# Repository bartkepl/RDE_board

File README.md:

# RDE (Resistance DEcade)
Resistance DEcade with SCPI, UART, USB, RS485 and ETHERNET in 3U eurocard format

---
## Status : WIP

- First revision of schematic and PCB is done. 
- Creating a complementary board with a DIN 41612 connector and other interface connectors to order a complete assembly and begin work on software and interface testing.

---
## Features:
- 2 layer board
- ARM Cortex-M33 Processor in LQFP48 (STM32G431CBT6) 
- 0 - 999k&#8486; ressistor-relay matrix driven by 6x STPIC6C595
- USB 2.0
- 10/100 Ethernet (based on WIZnet W5500)
- UART
- Half-duplex RS485 
- 3U eurocard IEEE 1101.1-1998 format (160x100 mm)
----

## License and Contribution

[MIT License](/LICENSE)

Open to contributions in both software and hardware!

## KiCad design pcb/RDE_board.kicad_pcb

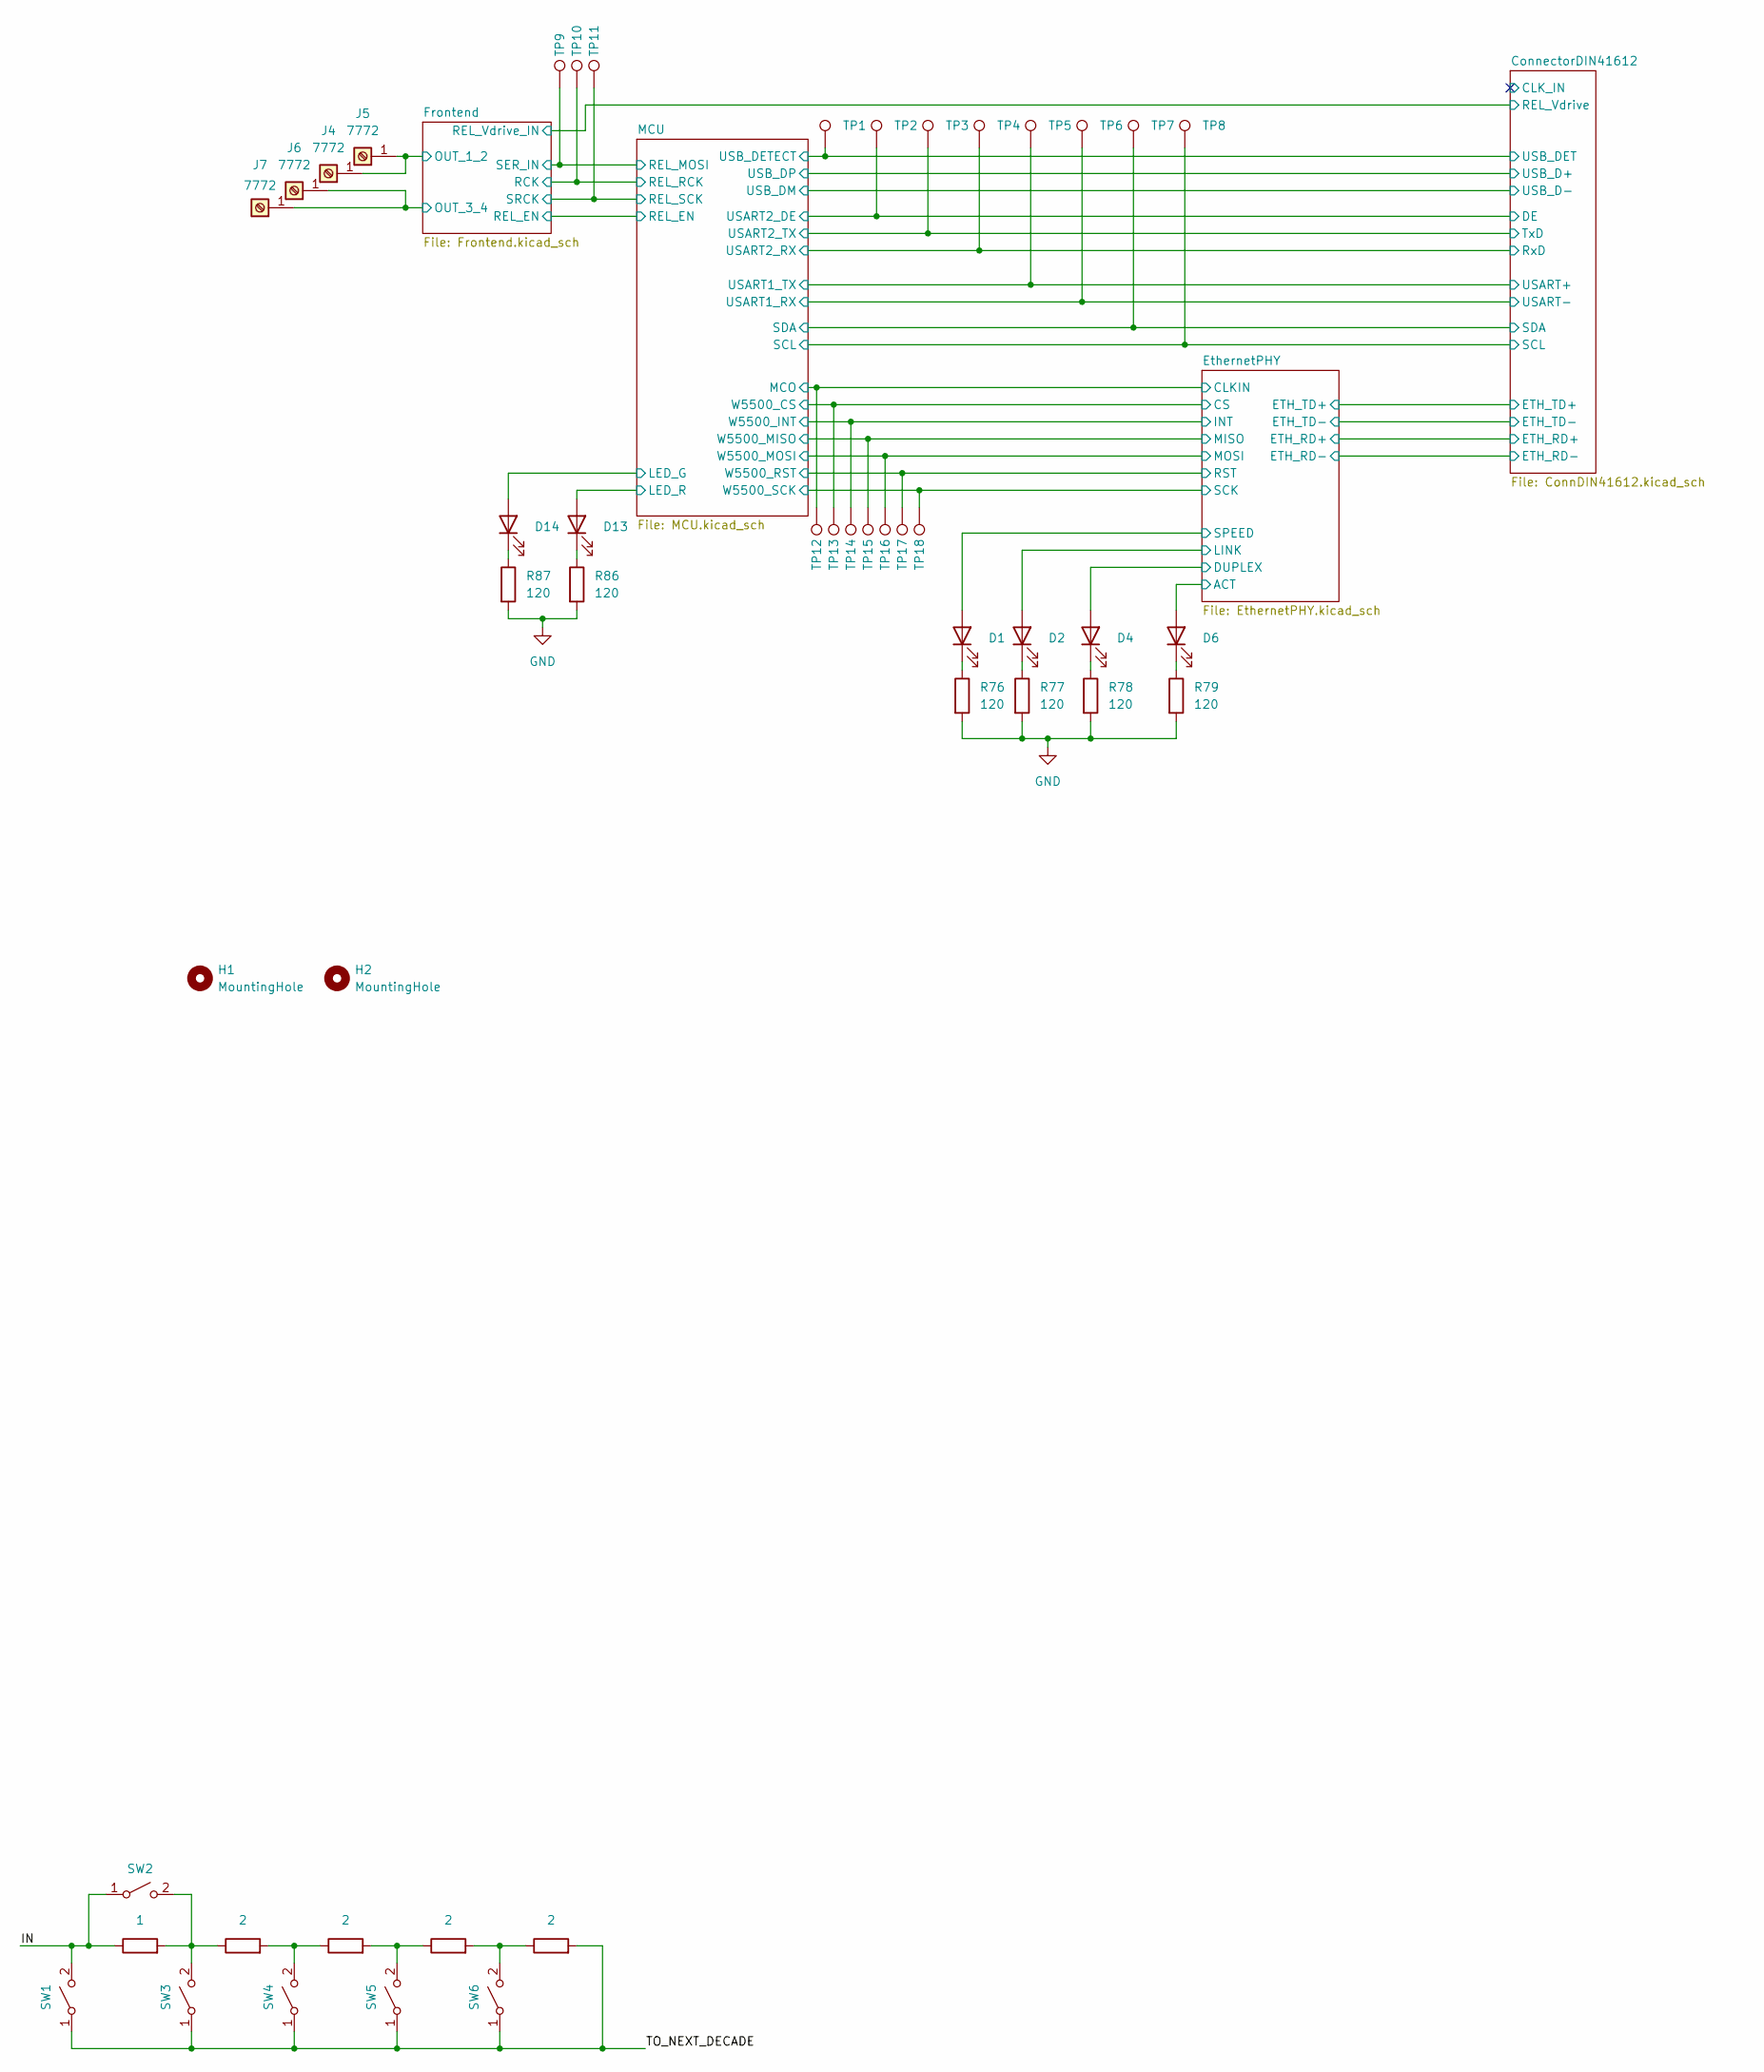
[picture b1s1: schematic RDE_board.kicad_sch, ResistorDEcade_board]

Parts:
D1, D2, D4, D6, D13, D14: LED_0603_1608Metric_Pad1.05x0.95mm_HandSolder
H1, H2: MountingHole; MountingHole_2.7mm_M2.5
J4, J5, J6, J7: 7772; Manufacturer_Part_Number 7772
R76, R77, R78, R79, R86, R87: 120; R_0603_1608Metric_Pad0.98x0.95mm_HandSolder
R92: 1; R_0603_1608Metric_Pad0.98x0.95mm_HandSolder
R93, R94, R95, R96: 2; R_0603_1608Metric_Pad0.98x0.95mm_HandSolder
SW1, SW2, SW3, SW4, SW5, SW6: SW_SPST
TP1, TP2, TP3, TP4, TP5, TP6, TP7, TP8, TP9, TP10, TP11, TP12, TP13, TP14, TP15, TP16, TP17, TP18: TestPoint; TestPoint_Pad_D1.0mm

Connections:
/ConnectorDIN41612/DE: TP2.1; also elsewhere on the board
/ConnectorDIN41612/RxD: TP4.1; also elsewhere on the board
/ConnectorDIN41612/TxD: TP3.1; also elsewhere on the board
/ConnectorDIN41612/USART+: TP5.1; also elsewhere on the board
/ConnectorDIN41612/USART-: TP6.1; also elsewhere on the board
/ConnectorDIN41612/USB_DET: TP1.1; also elsewhere on the board
/EthernetPHY/ACT: D6.2 (A); also elsewhere on the board
/EthernetPHY/CLKIN: TP12.1; also elsewhere on the board
/EthernetPHY/CS: TP13.1; also elsewhere on the board
/EthernetPHY/DUPLEX: D4.2 (A); also elsewhere on the board
/EthernetPHY/INT: TP14.1; also elsewhere on the board
/EthernetPHY/LINK: D2.2 (A); also elsewhere on the board
/EthernetPHY/MISO: TP15.1; also elsewhere on the board
/EthernetPHY/MOSI: TP16.1; also elsewhere on the board
/EthernetPHY/RST: TP17.1; also elsewhere on the board
/EthernetPHY/SCK: TP18.1; also elsewhere on the board
/EthernetPHY/SPEED: D1.2 (A); also elsewhere on the board
/Frontend/OUT_1_2: J4.1, J5.1; also elsewhere on the board
/Frontend/OUT_3_4: J6.1, J7.1; also elsewhere on the board
/Frontend/RCK: TP10.1; also elsewhere on the board
/Frontend/SER_IN: TP9.1; also elsewhere on the board
/Frontend/SRCK: TP11.1; also elsewhere on the board
/IN: R92.1, SW1.2 (B), SW2.1 (A)
/MCU/LED_G: D14.2 (A); also elsewhere on the board
/MCU/LED_R: D13.2 (A); also elsewhere on the board
/MCU/SCL: TP8.1; also elsewhere on the board
/MCU/SDA: TP7.1; also elsewhere on the board
/TO_NEXT_DECADE: R96.2, SW1.1 (A), SW3.1 (A), SW4.1 (A), SW5.1 (A), SW6.1 (A)
GND: R76.2, R77.2, R78.2, R79.2, R86.2, R87.2; also elsewhere on the board
unnamed: D1.1 (K), R76.1
unnamed: D2.1 (K), R77.1
unnamed: D4.1 (K), R78.1
unnamed: D6.1 (K), R79.1
unnamed: D13.1 (K), R86.1
unnamed: D14.1 (K), R87.1
unnamed: R92.2, R93.1, SW2.2 (B), SW3.2 (B)
unnamed: R93.2, R94.1, SW4.2 (B)
unnamed: R94.2, R95.1, SW5.2 (B)
unnamed: R95.2, R96.1, SW6.2 (B)

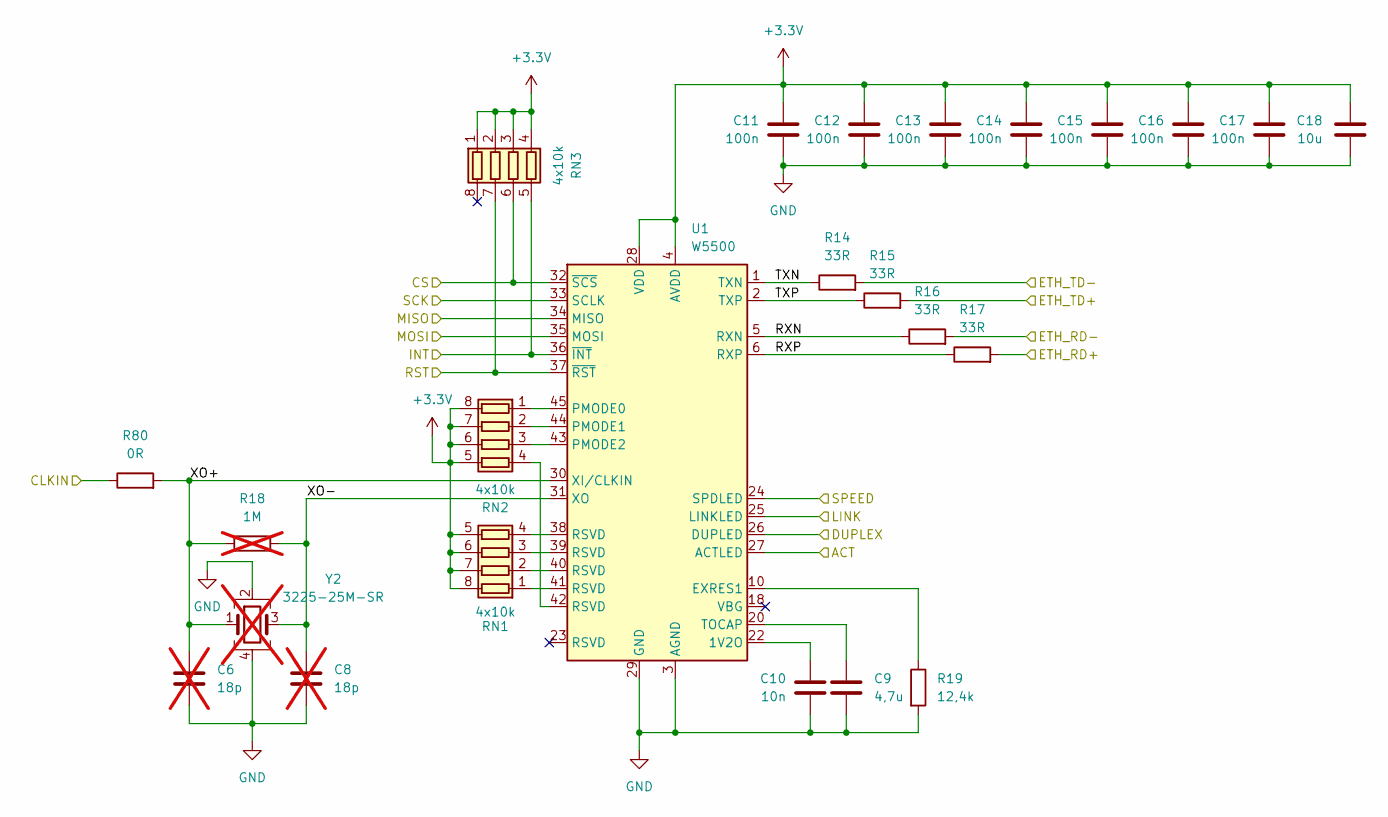
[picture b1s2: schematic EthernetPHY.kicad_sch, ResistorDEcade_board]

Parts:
C6, C8: 18p; C_0402_1005Metric_Pad0.74x0.62mm_HandSolder; not fitted
C9: 4,7u; C_0603_1608Metric_Pad1.08x0.95mm_HandSolder
C10: 10n; C_0603_1608Metric_Pad1.08x0.95mm_HandSolder
C11, C12, C13, C14, C15, C16, C17: 100n; C_0603_1608Metric_Pad1.08x0.95mm_HandSolder
C18: 10u; C_1206_3216Metric_Pad1.33x1.80mm_HandSolder
R14, R15, R16, R17: 33R; R_0603_1608Metric_Pad0.98x0.95mm_HandSolder
R18: 1M; R_0402_1005Metric_Pad0.72x0.64mm_HandSolder; not fitted
R19: 12,4k; R_0603_1608Metric_Pad0.98x0.95mm_HandSolder
R80: 0R; R_0402_1005Metric_Pad0.72x0.64mm_HandSolder
RN1, RN2, RN3: 4x10k; R_Array_Convex_4x0603
U1: W5500; LQFP-48_7x7mm_P0.5mm
Y2: 3225-25M-SR; Crystal_SMD_3225-4Pin_3.2x2.5mm; not fitted

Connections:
+3.3V: C11.2, C12.2, C13.2, C14.2, C15.2, C16.2, C17.2, C18.1, RN1.5 (R4.2), RN1.6 (R3.2), RN1.7 (R2.2), RN1.8 (R1.2), RN2.5 (R4.2), RN2.6 (R3.2), RN2.7 (R2.2), RN2.8 (R1.2), RN3.1 (R1.1), RN3.2 (R2.1), RN3.3 (R3.1), RN3.4 (R4.1), U1.4 (AVDD), U1.8 (AVDD), U1.11 (AVDD), U1.15 (AVDD), U1.17 (AVDD), U1.21 (AVDD), U1.28 (VDD); also elsewhere on the board
/ConnectorDIN41612/ETH_RD+: R17.2; also elsewhere on the board
/ConnectorDIN41612/ETH_RD-: R16.2; also elsewhere on the board
/ConnectorDIN41612/ETH_TD+: R15.2; also elsewhere on the board
/ConnectorDIN41612/ETH_TD-: R14.2; also elsewhere on the board
/EthernetPHY/ACT: U1.27 (ACTLED); also elsewhere on the board
/EthernetPHY/CLKIN: R80.1; also elsewhere on the board
/EthernetPHY/CS: RN3.6 (R3.2), U1.32 (~SCS); also elsewhere on the board
/EthernetPHY/DUPLEX: U1.26 (DUPLED); also elsewhere on the board
/EthernetPHY/INT: RN3.5 (R4.2), U1.36 (~INT); also elsewhere on the board
/EthernetPHY/LINK: U1.25 (LINKLED); also elsewhere on the board
/EthernetPHY/MISO: U1.34 (MISO); also elsewhere on the board
/EthernetPHY/MOSI: U1.35 (MOSI); also elsewhere on the board
/EthernetPHY/RST: RN3.7 (R2.2), U1.37 (~RST); also elsewhere on the board
/EthernetPHY/RXN: R16.1, U1.5 (RXN)
/EthernetPHY/RXP: R17.1, U1.6 (RXP)
/EthernetPHY/SCK: U1.33 (SCLK); also elsewhere on the board
/EthernetPHY/SPEED: U1.24 (SPDLED); also elsewhere on the board
/EthernetPHY/TXN: R14.1, U1.1 (TXN)
/EthernetPHY/TXP: R15.1, U1.2 (TXP)
/EthernetPHY/XO+: C6.1, R18.1, R80.2, U1.30 (XI/CLKIN), Y2.1
/EthernetPHY/XO-: C8.1, R18.2, U1.31 (XO), Y2.3
GND: C6.2, C8.2, C9.2, C10.1, C11.1, C12.1, C13.1, C14.1, C15.1, C16.1, C17.1, C18.2, R19.2, U1.3 (AGND), U1.9 (AGND), U1.14 (AGND), U1.16 (AGND), U1.19 (AGND), U1.29 (GND), U1.48 (AGND), Y2.2, Y2.4; also elsewhere on the board
unnamed: RN1.1 (R1.1), U1.41 (RSVD)
unnamed: RN1.2 (R2.1), U1.40 (RSVD)
unnamed: RN1.3 (R3.1), U1.39 (RSVD)
unnamed: RN1.4 (R4.1), U1.38 (RSVD)
unnamed: RN2.1 (R1.1), U1.45 (PMODE0)
unnamed: RN2.2 (R2.1), U1.44 (PMODE1)
unnamed: RN2.3 (R3.1), U1.43 (PMODE2)
unnamed: RN2.4 (R4.1), U1.42 (RSVD)
unnamed: C10.2, U1.22 (1V2O)
unnamed: R19.1, U1.10 (EXRES1)
unnamed: C9.1, U1.20 (TOCAP)

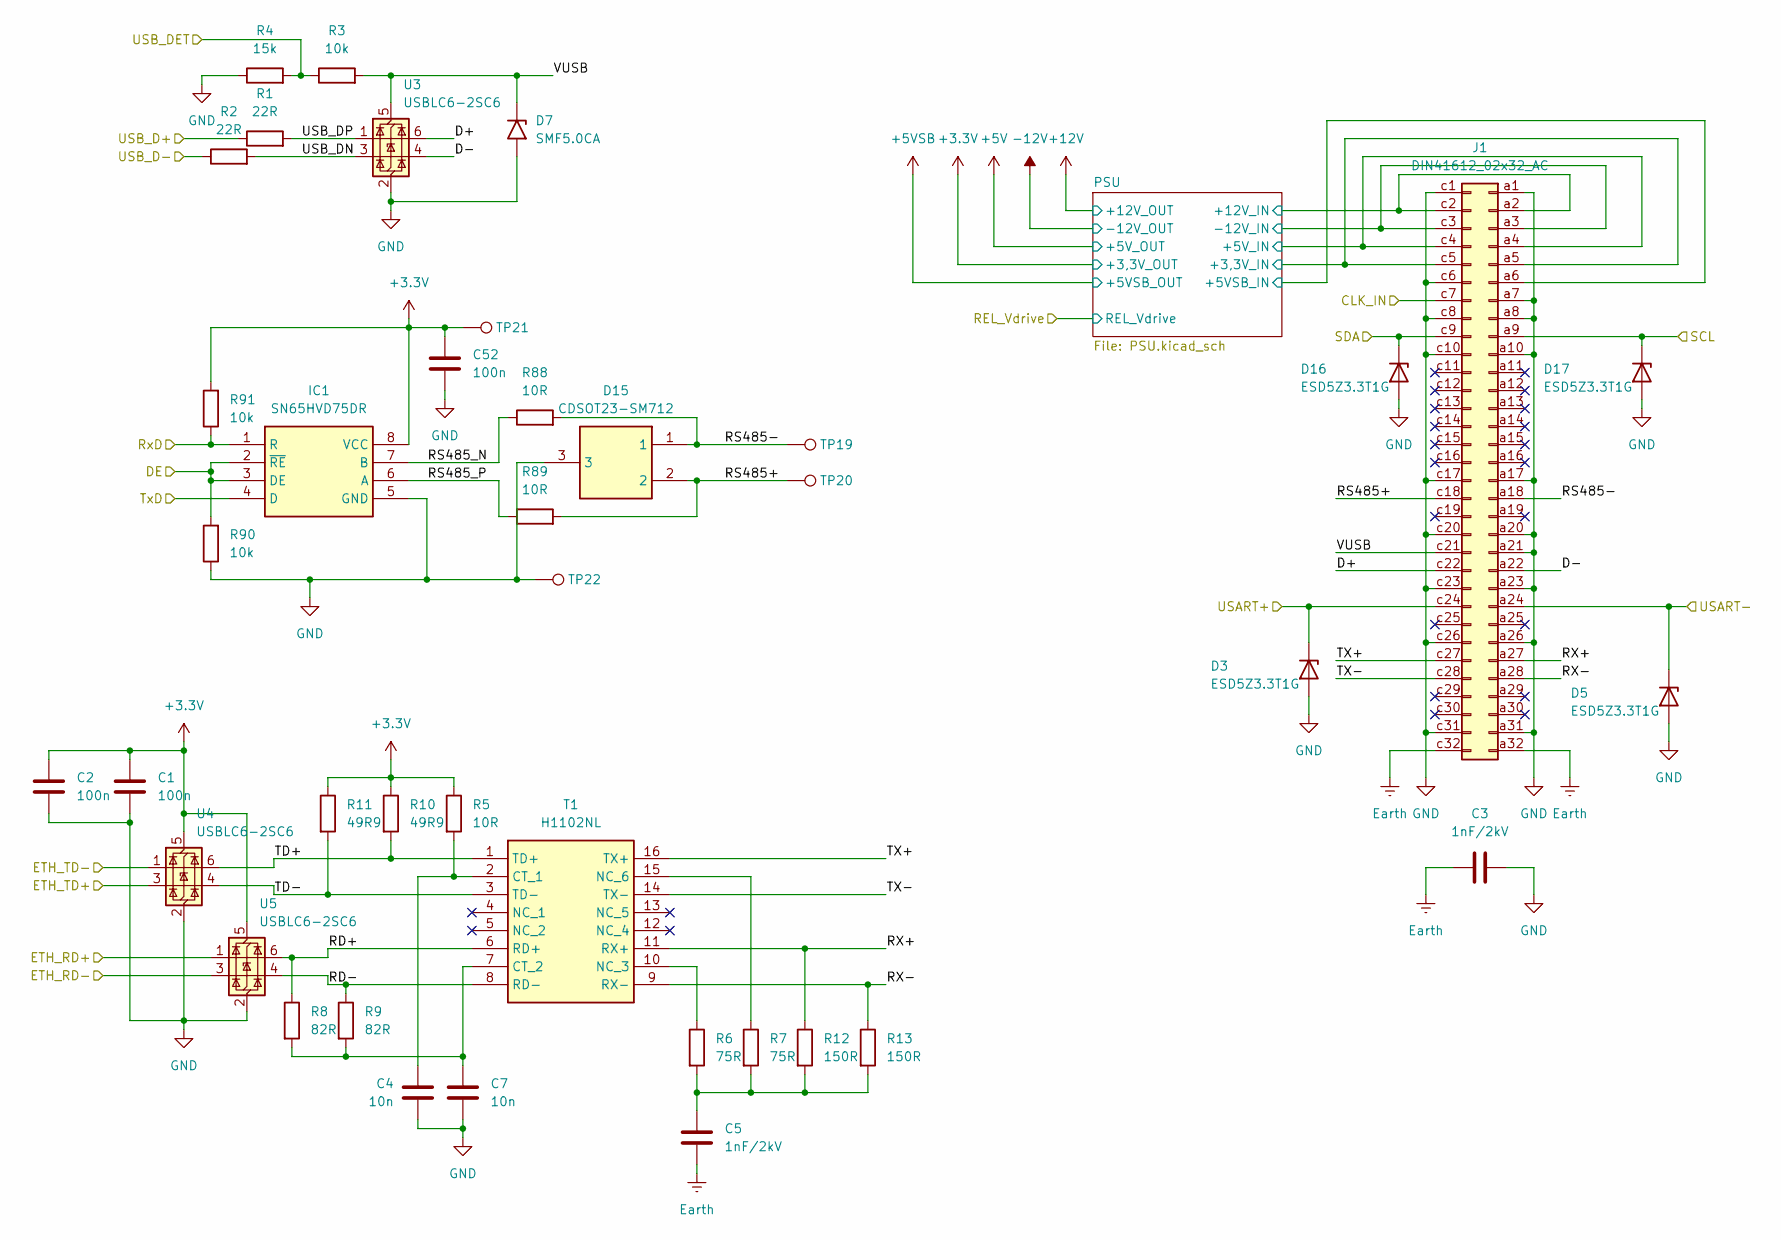
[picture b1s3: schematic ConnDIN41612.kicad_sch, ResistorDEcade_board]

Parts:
C1, C2, C52: 100n; C_0603_1608Metric_Pad1.08x0.95mm_HandSolder
C3, C5: 1nF/2kV; C_1206_3216Metric_Pad1.33x1.80mm_HandSolder
C4, C7: 10n; C_0603_1608Metric_Pad1.08x0.95mm_HandSolder
D3, D5, D16, D17: ESD5Z3.3T1G; D_SOD-523
D7: SMF5.0CA; D_SMF
D15: CDSOT23-SM712; SOT95P230X117-3N; Manufacturer_Part_Number CDSOT23-SM712
IC1: SN65HVD75DR; SOIC127P600X175-8N; Manufacturer_Part_Number SN65HVD75DR
J1: DIN41612_02x32_AC; DIN41612_C_2x32_Male_Horizontal_THT
R1, R2: 22R; R_0402_1005Metric_Pad0.72x0.64mm_HandSolder
R3, R90, R91: 10k; R_0603_1608Metric_Pad0.98x0.95mm_HandSolder
R4: 15k; R_0603_1608Metric_Pad0.98x0.95mm_HandSolder
R5, R88, R89: 10R; R_0603_1608Metric_Pad0.98x0.95mm_HandSolder
R6, R7: 75R; R_0603_1608Metric_Pad0.98x0.95mm_HandSolder
R8, R9: 82R; R_0603_1608Metric_Pad0.98x0.95mm_HandSolder
R10, R11: 49R9; R_0603_1608Metric_Pad0.98x0.95mm_HandSolder
R12, R13: 150R; R_0603_1608Metric_Pad0.98x0.95mm_HandSolder
T1: H1102NL; SOIC127P940X597-16N; Manufacturer_Part_Number H1102NL
TP19, TP20, TP21, TP22: TestPoint; TestPoint_Pad_D1.0mm
U3, U4, U5: USBLC6-2SC6; SOT-23-6_Handsoldering

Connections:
+3.3V: C1.1, C2.1, C52.1, IC1.8 (VCC), R5.1, R10.1, R11.1, R91.2, TP21.1, U4.5 (VBUS), U5.5 (VBUS); also elsewhere on the board
/ConnectorDIN41612/CLK_IN: J1.c7
/ConnectorDIN41612/D+: J1.c22, U3.6 (I/O1)
/ConnectorDIN41612/D-: J1.a22, U3.4 (I/O2)
/ConnectorDIN41612/DE: IC1.2 (~RE), IC1.3 (DE), R90.2; also elsewhere on the board
/ConnectorDIN41612/ETH_RD+: U5.1 (I/O1); also elsewhere on the board
/ConnectorDIN41612/ETH_RD-: U5.3 (I/O2); also elsewhere on the board
/ConnectorDIN41612/ETH_TD+: U4.3 (I/O2); also elsewhere on the board
/ConnectorDIN41612/ETH_TD-: U4.1 (I/O1); also elsewhere on the board
/ConnectorDIN41612/PSU/+3,3V_IN: J1.a5, J1.c5; also elsewhere on the board
/ConnectorDIN41612/PSU/+5VSB_IN: J1.a6
/ConnectorDIN41612/PSU/+5V_IN: J1.a4, J1.c4; also elsewhere on the board
/ConnectorDIN41612/PSU/+12V_IN: J1.a2, J1.c2
/ConnectorDIN41612/PSU/-12V_IN: J1.a3, J1.c3
/ConnectorDIN41612/RD+: R8.1, T1.6 (RD+), U5.6 (I/O1)
/ConnectorDIN41612/RD-: R9.1, T1.8 (RD-), U5.4 (I/O2)
/ConnectorDIN41612/RS485+: D15.2, J1.c18, R89.2, TP20.1
/ConnectorDIN41612/RS485-: D15.1, J1.a18, R88.2, TP19.1
/ConnectorDIN41612/RS485_N: IC1.7 (B), R88.1
/ConnectorDIN41612/RS485_P: IC1.6 (A), R89.1
/ConnectorDIN41612/RX+: J1.a27, R12.1, T1.11 (RX+)
/ConnectorDIN41612/RX-: J1.a28, R13.1, T1.9 (RX-)
/ConnectorDIN41612/RxD: IC1.1 (R), R91.1; also elsewhere on the board
/ConnectorDIN41612/TD+: R10.2, T1.1 (TD+), U4.6 (I/O1)
/ConnectorDIN41612/TD-: R11.2, T1.3 (TD-), U4.4 (I/O2)
/ConnectorDIN41612/TX+: J1.c27, T1.16 (TX+)
/ConnectorDIN41612/TX-: J1.c28, T1.14 (TX-)
/ConnectorDIN41612/TxD: IC1.4 (D); also elsewhere on the board
/ConnectorDIN41612/USART+: D3.1 (K), J1.c24; also elsewhere on the board
/ConnectorDIN41612/USART-: D5.1 (K), J1.a24; also elsewhere on the board
/ConnectorDIN41612/USB_D+: R1.1; also elsewhere on the board
/ConnectorDIN41612/USB_D-: R2.1; also elsewhere on the board
/ConnectorDIN41612/USB_DET: R3.1, R4.2; also elsewhere on the board
/ConnectorDIN41612/USB_DN: R2.2, U3.3 (I/O2)
/ConnectorDIN41612/USB_DP: R1.2, U3.1 (I/O1)
/ConnectorDIN41612/VUSB: D7.1 (A1), J1.c21, R3.2, U3.5 (VBUS)
/MCU/SCL: D17.1 (K), J1.a9; also elsewhere on the board
/MCU/SDA: D16.1 (K), J1.c9; also elsewhere on the board
Earth: C3.1, C5.2, J1.a32, J1.c32
GND: C1.2, C2.2, C3.2, C4.1, C7.2, C52.2, D3.2 (A), D5.2 (A), D7.2 (A2), D15.3, D16.2 (A), D17.2 (A), IC1.5 (GND), J1.a1, J1.a7, J1.a8, J1.a10, J1.a17, J1.a20, J1.a21, J1.a23, J1.a26, J1.a31, J1.c1, J1.c6, J1.c8, J1.c10, J1.c17, J1.c20, J1.c23, J1.c26, J1.c31, R4.1, R90.1, TP22.1, U3.2 (GND), U4.2 (GND), U5.2 (GND); also elsewhere on the board
unnamed: C5.1, R6.2, R7.2, R12.2, R13.2
unnamed: C4.2, R5.2, T1.2 (CT_1)
unnamed: C7.1, R8.2, R9.2, T1.7 (CT_2)
unnamed: R6.1, T1.10 (NC_3)
unnamed: R7.1, T1.15 (NC_6)

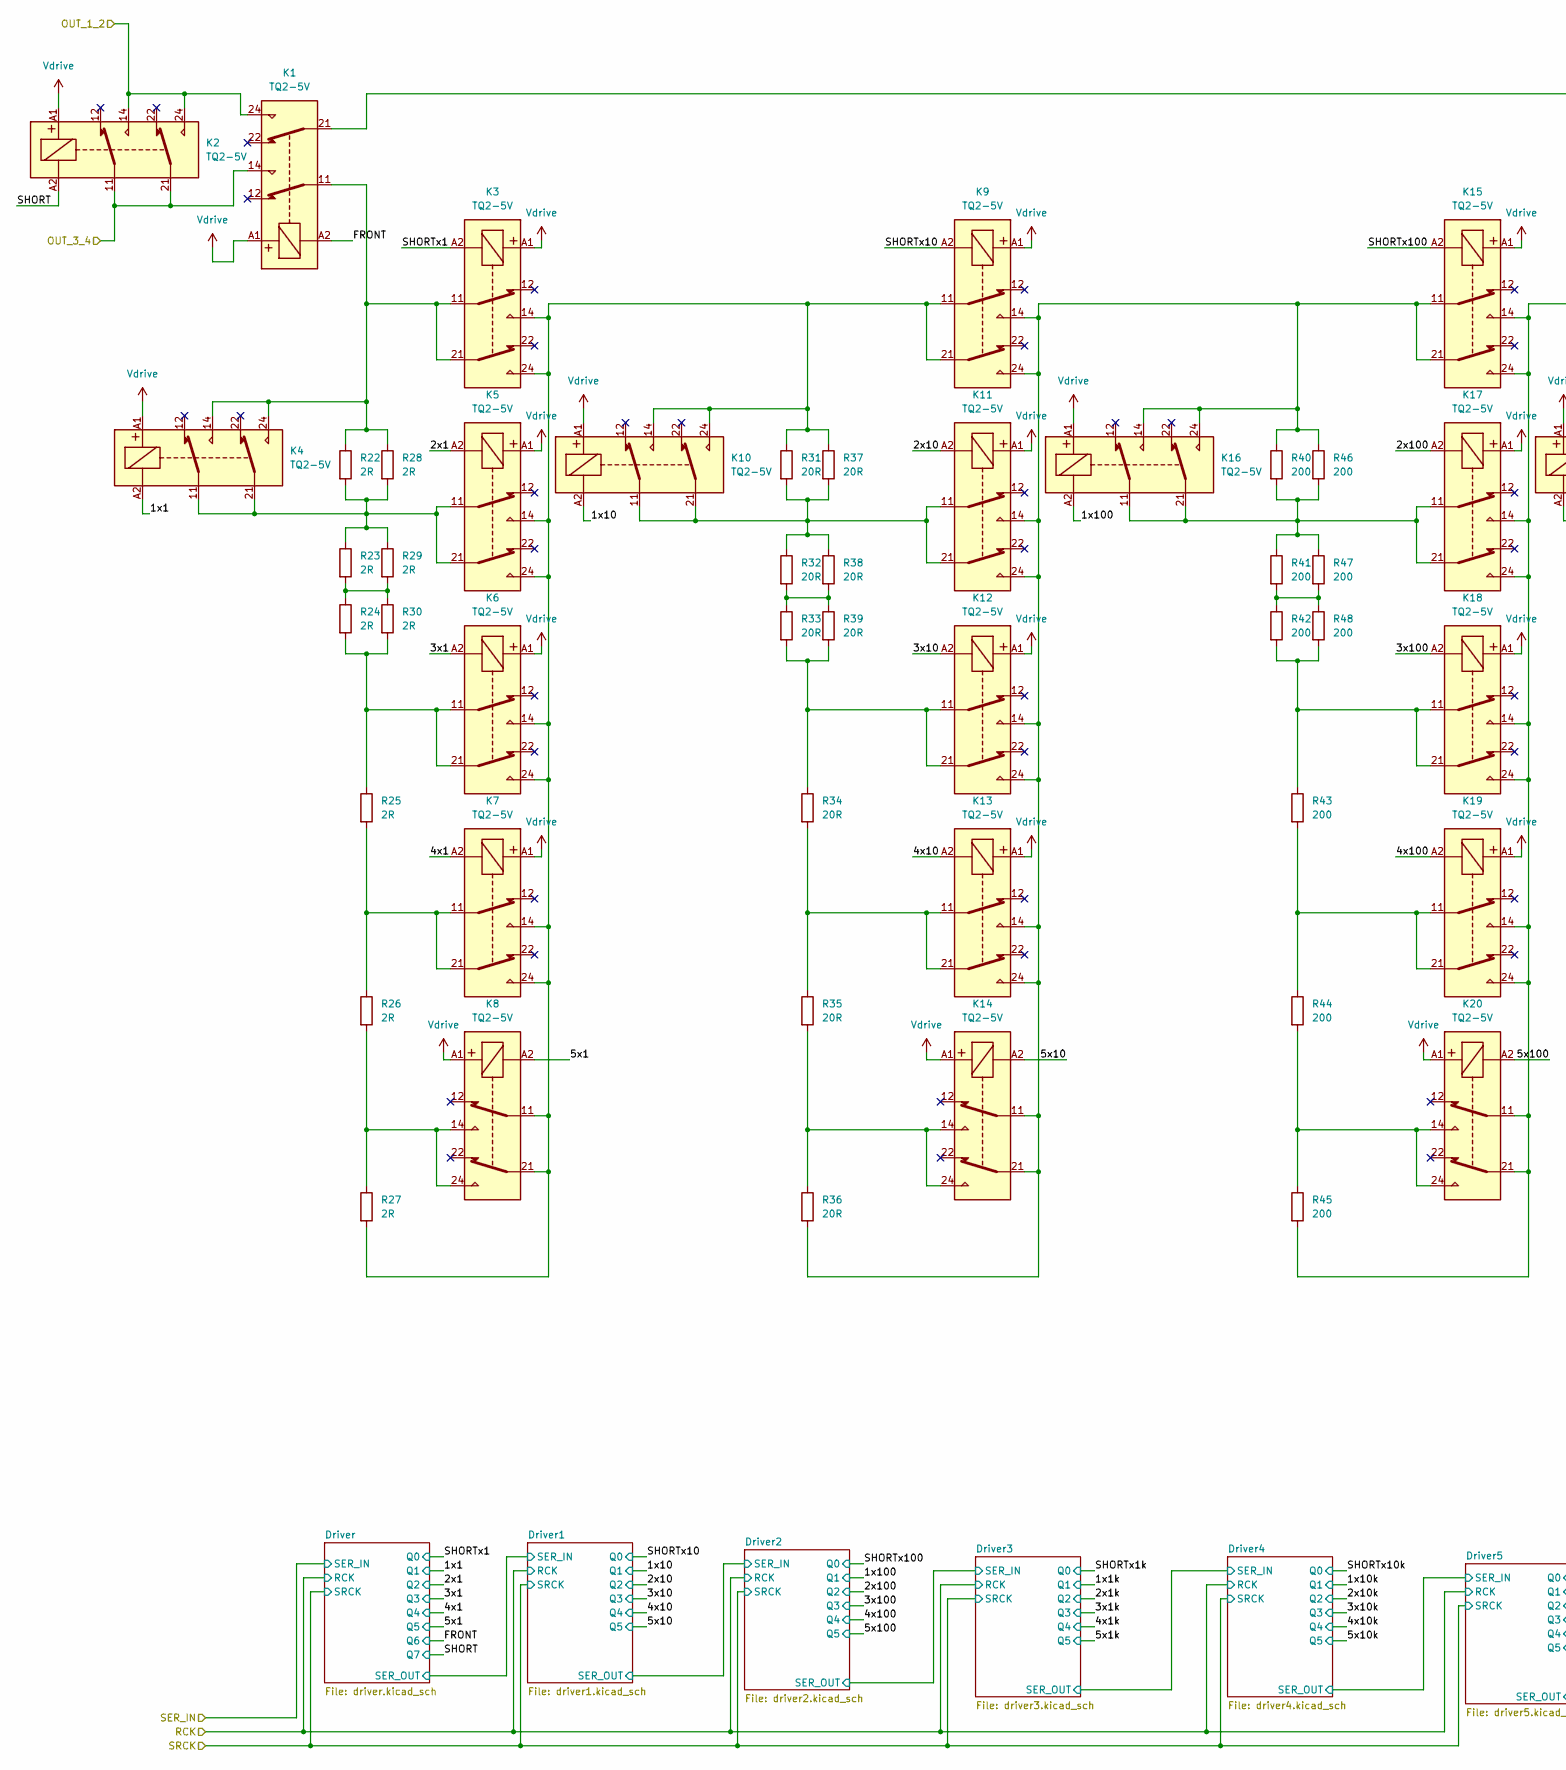
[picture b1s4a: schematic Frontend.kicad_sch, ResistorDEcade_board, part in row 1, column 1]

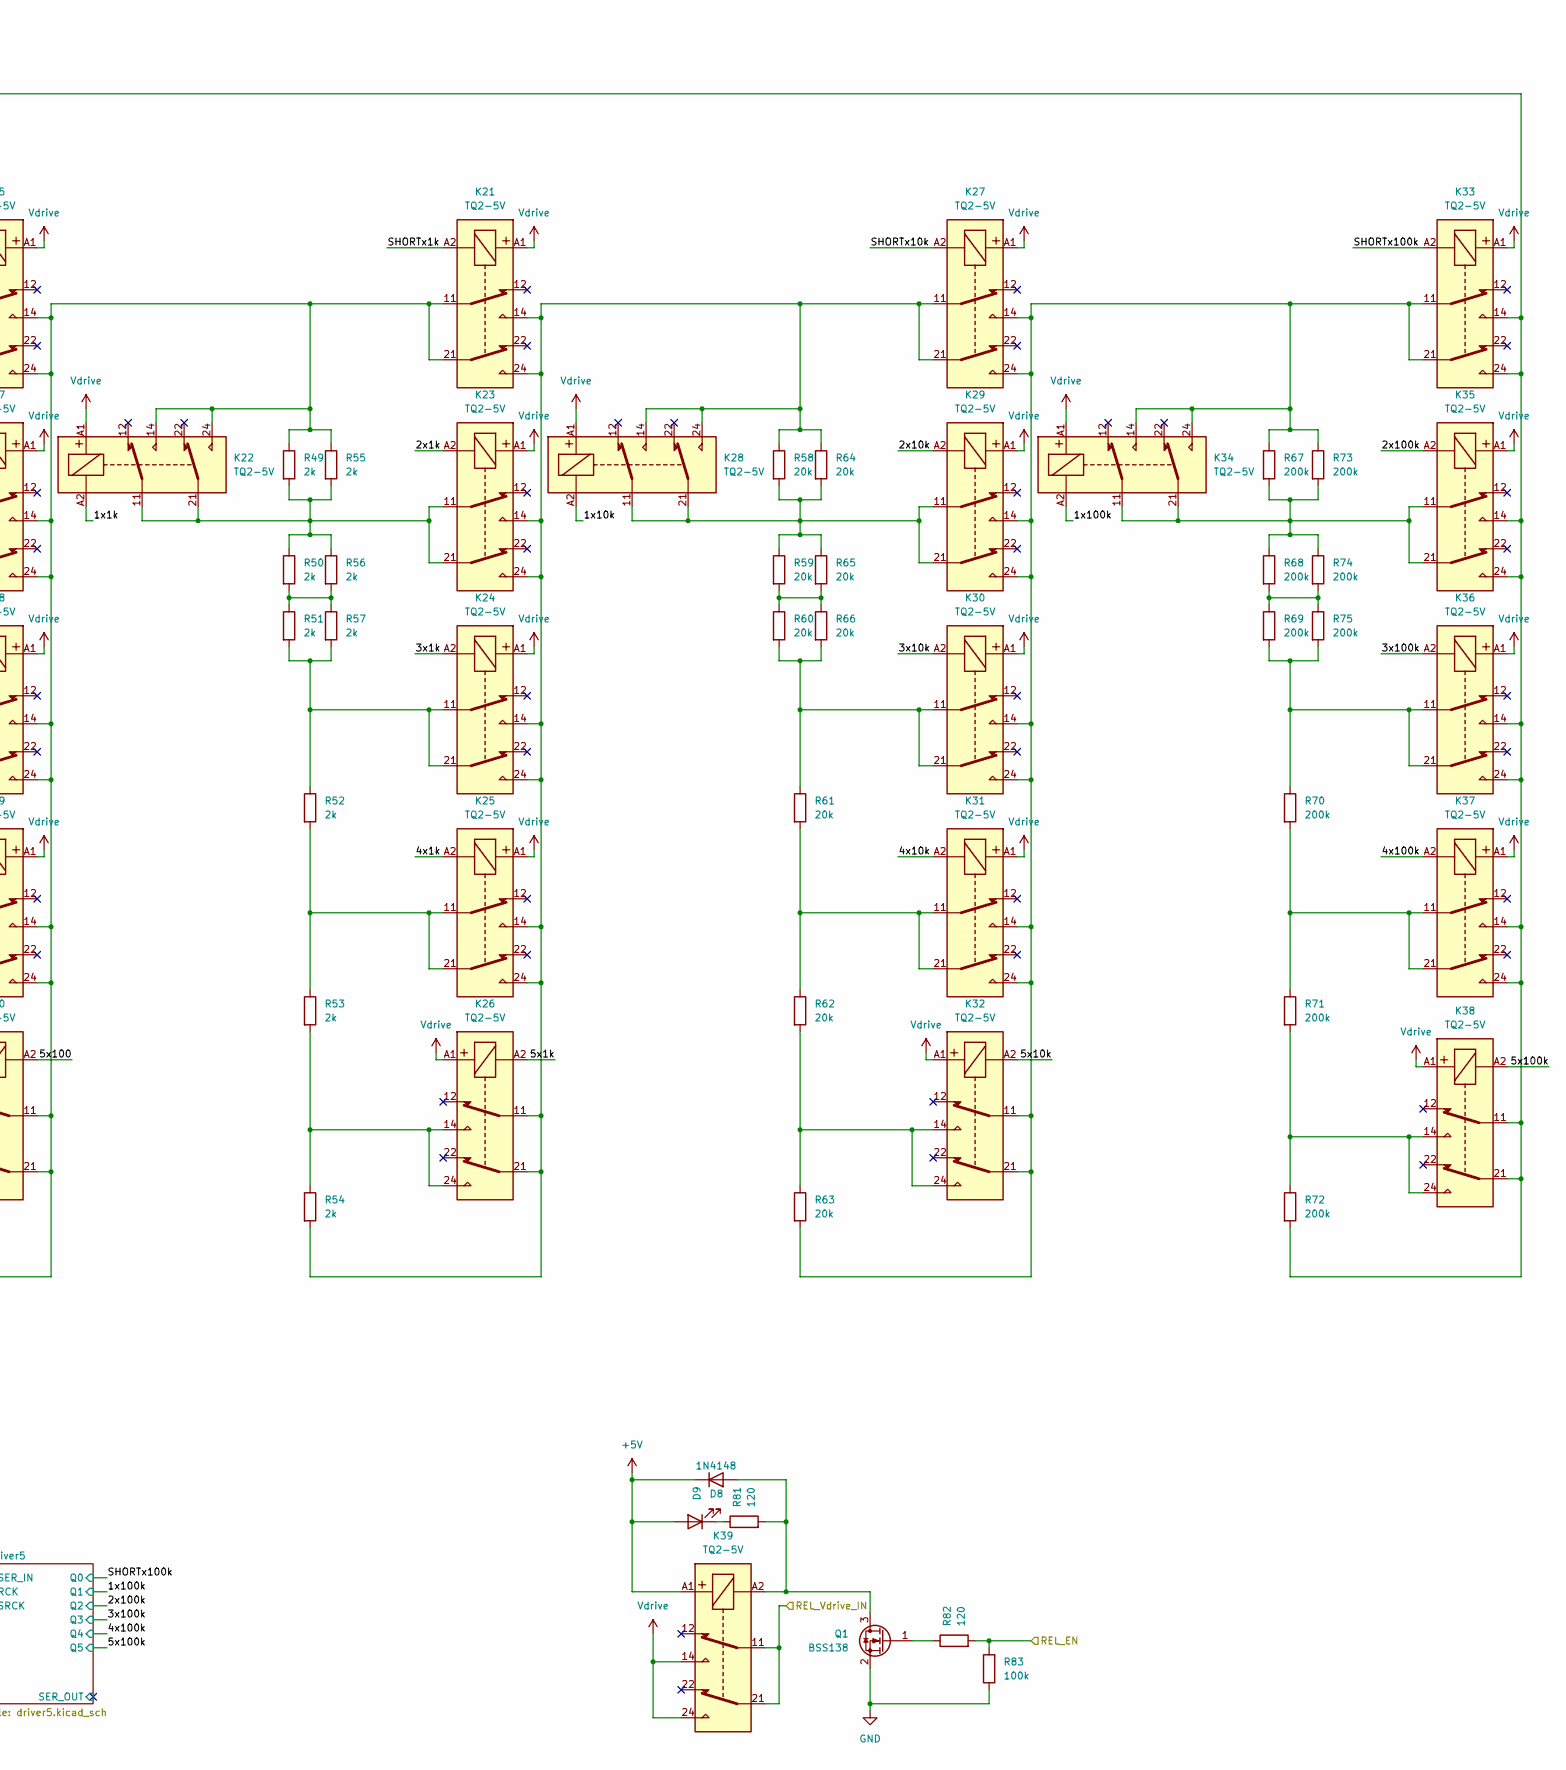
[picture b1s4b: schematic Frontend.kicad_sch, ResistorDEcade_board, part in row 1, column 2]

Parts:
D8: 1N4148; D_MiniMELF
D9: LED_0603_1608Metric_Pad1.05x0.95mm_HandSolder
K1, K2, K3, K4, K5, K6, K7, K8, K9, K10, K11, K12, K13, K14, K15, K16, K17, K18, K19, K20, K21, K22, K23, K24, K25, K26, K27, K28, K29, K30, K31, K32, K33, K34, K35, K36, K37, K38, K39: TQ2-5V; TX2L25V; Manufacturer_Part_Number TQ2-5V
Q1: BSS138; SOT-23
R22, R23, R24, R25, R26, R27, R28, R29, R30: 2R; R_0603_1608Metric_Pad0.98x0.95mm_HandSolder
R31, R32, R33, R34, R35, R36, R37, R38, R39: 20R; R_0603_1608Metric_Pad0.98x0.95mm_HandSolder
R40, R41, R42, R43, R44, R45, R46, R47, R48: 200; R_0603_1608Metric_Pad0.98x0.95mm_HandSolder
R49, R50, R51, R52, R53, R54, R55, R56, R57: 2k; R_0603_1608Metric_Pad0.98x0.95mm_HandSolder
R58, R59, R60, R61, R62, R63, R64, R65, R66: 20k; R_0603_1608Metric_Pad0.98x0.95mm_HandSolder
R67, R68, R69, R70, R71, R72, R73, R74, R75: 200k; R_0603_1608Metric_Pad0.98x0.95mm_HandSolder
R81, R82: 120; R_0603_1608Metric_Pad0.98x0.95mm_HandSolder
R83: 100k; R_0603_1608Metric_Pad0.98x0.95mm_HandSolder

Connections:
+5V: D8.1 (K), D9.2 (A), K39.A1; also elsewhere on the board
/ConnectorDIN41612/REL_Vdrive: K39.11, K39.21; also elsewhere on the board
/Frontend/1x1: K4.A2; also elsewhere on the board
/Frontend/1x1k: K22.A2; also elsewhere on the board
/Frontend/1x10: K10.A2; also elsewhere on the board
/Frontend/1x10k: K28.A2; also elsewhere on the board
/Frontend/1x100: K16.A2; also elsewhere on the board
/Frontend/1x100k: K34.A2; also elsewhere on the board
/Frontend/2x1: K5.A2; also elsewhere on the board
/Frontend/2x1k: K23.A2; also elsewhere on the board
/Frontend/2x10: K11.A2; also elsewhere on the board
/Frontend/2x10k: K29.A2; also elsewhere on the board
/Frontend/2x100: K17.A2; also elsewhere on the board
/Frontend/2x100k: K35.A2; also elsewhere on the board
/Frontend/3x1: K6.A2; also elsewhere on the board
/Frontend/3x1k: K24.A2; also elsewhere on the board
/Frontend/3x10: K12.A2; also elsewhere on the board
/Frontend/3x10k: K30.A2; also elsewhere on the board
/Frontend/3x100: K18.A2; also elsewhere on the board
/Frontend/3x100k: K36.A2; also elsewhere on the board
/Frontend/4x1: K7.A2; also elsewhere on the board
/Frontend/4x1k: K25.A2; also elsewhere on the board
/Frontend/4x10: K13.A2; also elsewhere on the board
/Frontend/4x10k: K31.A2; also elsewhere on the board
/Frontend/4x100: K19.A2; also elsewhere on the board
/Frontend/4x100k: K37.A2; also elsewhere on the board
/Frontend/5x1: K8.A2; also elsewhere on the board
/Frontend/5x1k: K26.A2; also elsewhere on the board
/Frontend/5x10: K14.A2; also elsewhere on the board
/Frontend/5x10k: K32.A2; also elsewhere on the board
/Frontend/5x100: K20.A2; also elsewhere on the board
/Frontend/5x100k: K38.A2; also elsewhere on the board
/Frontend/FRONT: K1.A2; also elsewhere on the board
/Frontend/OUT_1_2: K1.24, K2.14, K2.24; also elsewhere on the board
/Frontend/OUT_3_4: K1.14, K2.11, K2.21; also elsewhere on the board
/Frontend/REL_EN: R82.2, R83.2; also elsewhere on the board
/Frontend/SHORT: K2.A2; also elsewhere on the board
/Frontend/SHORTx1: K3.A2; also elsewhere on the board
/Frontend/SHORTx1k: K21.A2; also elsewhere on the board
/Frontend/SHORTx10: K9.A2; also elsewhere on the board
/Frontend/SHORTx10k: K27.A2; also elsewhere on the board
/Frontend/SHORTx100: K15.A2; also elsewhere on the board
/Frontend/SHORTx100k: K33.A2; also elsewhere on the board
GND: Q1.2 (S), R83.1; also elsewhere on the board
unnamed: D8.2 (A), K39.A2, Q1.3 (D), R81.2
unnamed: D9.1 (K), R81.1
unnamed: K1.11, K3.11, K3.21, K4.14, K4.24, R22.1, R28.1
unnamed: K1.21, K33.14, K33.24, K35.14, K35.24, K36.14, K36.24, K37.14, K37.24, K38.11, K38.21, R72.2
unnamed: K4.11, K4.21, K5.11, K5.21, R22.2, R23.1, R28.2, R29.1
unnamed: K6.11, K6.21, R24.2, R25.1, R30.2
unnamed: K7.11, K7.21, R25.2, R26.1
unnamed: K8.14, K8.24, R26.2, R27.1
unnamed: K10.11, K10.21, K11.11, K11.21, R31.2, R32.1, R37.2, R38.1
unnamed: K3.14, K3.24, K5.14, K5.24, K6.14, K6.24, K7.14, K7.24, K8.11, K8.21, K9.11, K9.21, K10.14, K10.24, R27.2, R31.1, R37.1
unnamed: K9.14, K9.24, K11.14, K11.24, K12.14, K12.24, K13.14, K13.24, K14.11, K14.21, K15.11, K15.21, K16.14, K16.24, R36.2, R40.1, R46.1
unnamed: K12.11, K12.21, R33.2, R34.1, R39.2
unnamed: K13.11, K13.21, R34.2, R35.1
unnamed: K14.14, K14.24, R35.2, R36.1
unnamed: K15.14, K15.24, K17.14, K17.24, K18.14, K18.24, K19.14, K19.24, K20.11, K20.21, K21.11, K21.21, K22.14, K22.24, R45.2, R49.1, R55.1
unnamed: K16.11, K16.21, K17.11, K17.21, R40.2, R41.1, R46.2, R47.1
unnamed: K18.11, K18.21, R42.2, R43.1, R48.2
unnamed: K19.11, K19.21, R43.2, R44.1
unnamed: K20.14, K20.24, R44.2, R45.1
unnamed: K21.14, K21.24, K23.14, K23.24, K24.14, K24.24, K25.14, K25.24, K26.11, K26.21, K27.11, K27.21, K28.14, K28.24, R54.2, R58.1, R64.1
unnamed: K22.11, K22.21, K23.11, K23.21, R49.2, R50.1, R55.2, R56.1
unnamed: K24.11, K24.21, R51.2, R52.1, R57.2
unnamed: K25.11, K25.21, R52.2, R53.1
unnamed: K26.14, K26.24, R53.2, R54.1
unnamed: K27.14, K27.24, K29.14, K29.24, K30.14, K30.24, K31.14, K31.24, K32.11, K32.21, K33.11, K33.21, K34.14, K34.24, R63.2, R67.1, R73.1
unnamed: K28.11, K28.21, K29.11, K29.21, R58.2, R59.1, R64.2, R65.1
unnamed: K30.11, K30.21, R60.2, R61.1, R66.2
unnamed: K31.11, K31.21, R61.2, R62.1
unnamed: K32.14, K32.24, R62.2, R63.1
unnamed: K34.11, K34.21, K35.11, K35.21, R67.2, R68.1, R73.2, R74.1
unnamed: K36.11, K36.21, R69.2, R70.1, R75.2
unnamed: K37.11, K37.21, R70.2, R71.1
unnamed: K38.14, K38.24, R71.2, R72.1
unnamed: Q1.1 (G), R82.1
unnamed: R23.2, R24.1, R29.2, R30.1
unnamed: R32.2, R33.1, R38.2, R39.1
unnamed: R41.2, R42.1, R47.2, R48.1
unnamed: R50.2, R51.1, R56.2, R57.1
unnamed: R59.2, R60.1, R65.2, R66.1
unnamed: R68.2, R69.1, R74.2, R75.1
Vdrive: K1.A1, K2.A1, K3.A1, K4.A1, K5.A1, K6.A1, K7.A1, K8.A1, K9.A1, K10.A1, K11.A1, K12.A1, K13.A1, K14.A1, K15.A1, K16.A1, K17.A1, K18.A1, K19.A1, K20.A1, K21.A1, K22.A1, K23.A1, K24.A1, K25.A1, K26.A1, K27.A1, K28.A1, K29.A1, K30.A1, K31.A1, K32.A1, K33.A1, K34.A1, K35.A1, K36.A1, K37.A1, K38.A1, K39.14, K39.24; also elsewhere on the board

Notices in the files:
firmware/RDE_soft/App/wiznet/Ethernet/wizchip_conf.h:
Copyright (c)  2013, WIZnet Co., LTD.
All rights reserved.
